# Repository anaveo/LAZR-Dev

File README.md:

# LAZR-Dev
LAZR is a remote which uses hand gestures to control functions of a TV. I undertook this project to understand IR signals and learn Autodesk Eagle, a PCB design software.

For more information click [here](https://omanavekar.wixsite.com/ommakes/lazr) to access LAZR's page on [omlabs.me](https://omanavekar.wixsite.com/ommakes)

## Components
| Plugin | Quantity | Description |
| ------ | ------ | ------ |
| Node MCU | 1 | Microcontroller Unit |
| Flex Sensor | 5 | Sense finger movement |
| 1k Resistor | 5 | Voltage dividing resistor for flex sensor |
| 74HX4051N | 1 | Multiplexer IC for sensors |
| DIP-8 IC Socket | 1 | Multiplexer IC mount |
| Pin Header | 40 | - |
| Jumper Cable | 10 | - |
| Glove | 1 | - |
| PCB | 1 | - |

## Software
* [Arduino IDE](https://www.arduino.cc/en/main/software) - Programming environment
* [Autodesk EAGLE](https://www.autodesk.com/products/eagle/overview?plc=F360&term=1-YEAR&support=ADVANCED&quantity=1) - Schematic and PCB design software

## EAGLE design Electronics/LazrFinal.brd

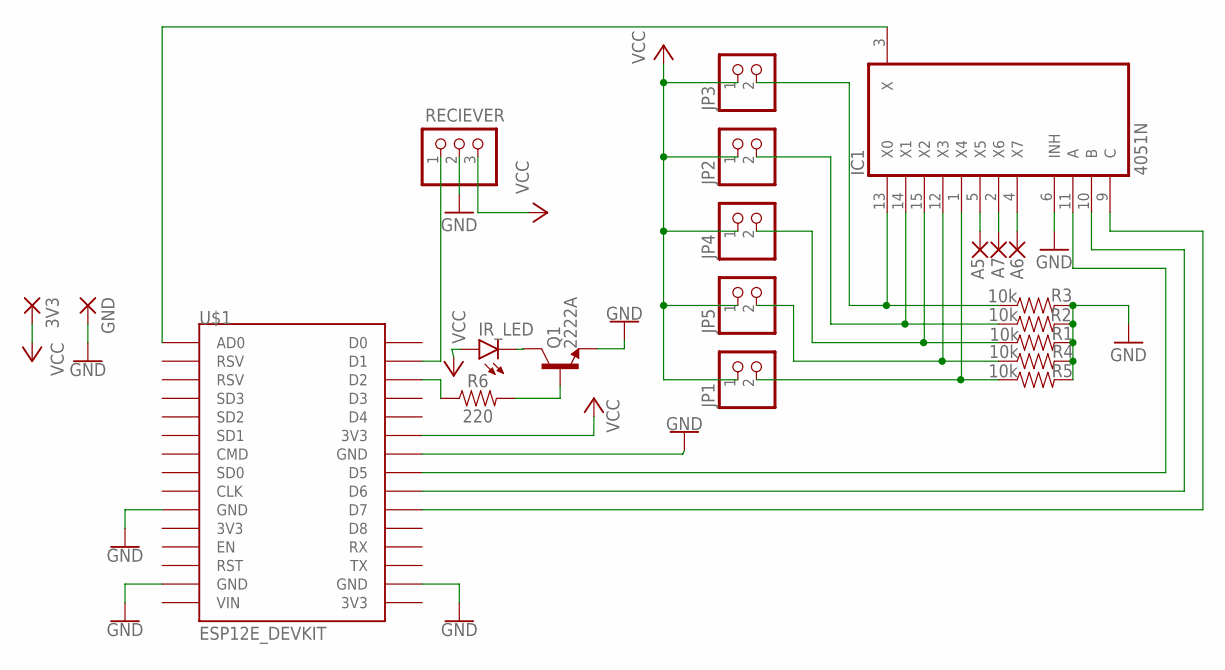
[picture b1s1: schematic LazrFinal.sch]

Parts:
3V3: SMD5; SMD2,54-5,08
A5, A6, A7: SMD2; SMD1,27-2,54
GND: SMD5; SMD2,54-5,08
IC1: 4051N; DIL16
IR_LED: LED-IRTSAL6100; LED_5MM
JP1, JP2, JP3, JP4, JP5: PINHD-1X2; 1X02
Q1: 2222A; TO-92
R1, R2, R3, R4, R5: 10k; AXIAL-0.3
R6: 220; AXIAL-0.3
RECIEVER: PINHD-1X3; 1X03
U$1: ESP12E_DEVKIT

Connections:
GND: GND.1, IC1.6 (INH), IC1.8 (GND), Q1.1 (E), R1.P$2 (2), R2.P$2 (2), R3.P$2 (2), R4.P$2 (2), R5.P$2 (2), RECIEVER.2, U$1.GND@0 (GND), U$1.GND@1 (GND), U$1.GND@2 (GND), U$1.GND@3 (GND)
unnamed: IC1.3 (X), U$1.AD0
unnamed: IC1.11 (A), U$1.D5
unnamed: IC1.10 (B), U$1.D6
unnamed: IC1.9 (C), U$1.D7
unnamed: IC1.13 (X0), JP3.2, R3.P$1 (1)
unnamed: IC1.14 (X1), JP2.2, R2.P$1 (1)
unnamed: IC1.15 (X2), JP4.2, R1.P$1 (1)
unnamed: IC1.12 (X3), JP5.2, R4.P$1 (1)
unnamed: IC1.1 (X4), JP1.2, R5.P$1 (1)
unnamed: R6.P$1 (1), U$1.D2
unnamed: RECIEVER.1, U$1.D1
unnamed: IR_LED.K (C), Q1.3 (C)
unnamed: Q1.2 (B), R6.P$2 (2)
unnamed: A5.1, IC1.5 (X5)
unnamed: A7.1, IC1.2 (X6)
unnamed: A6.1, IC1.4 (X7)
VCC: 3V3.1, IC1.16 (VCC), IR_LED.A, JP1.1, JP2.1, JP3.1, JP4.1, JP5.1, RECIEVER.3, U$1.3V3@1 (3V3)
VEE: IC1.7 (VEE)

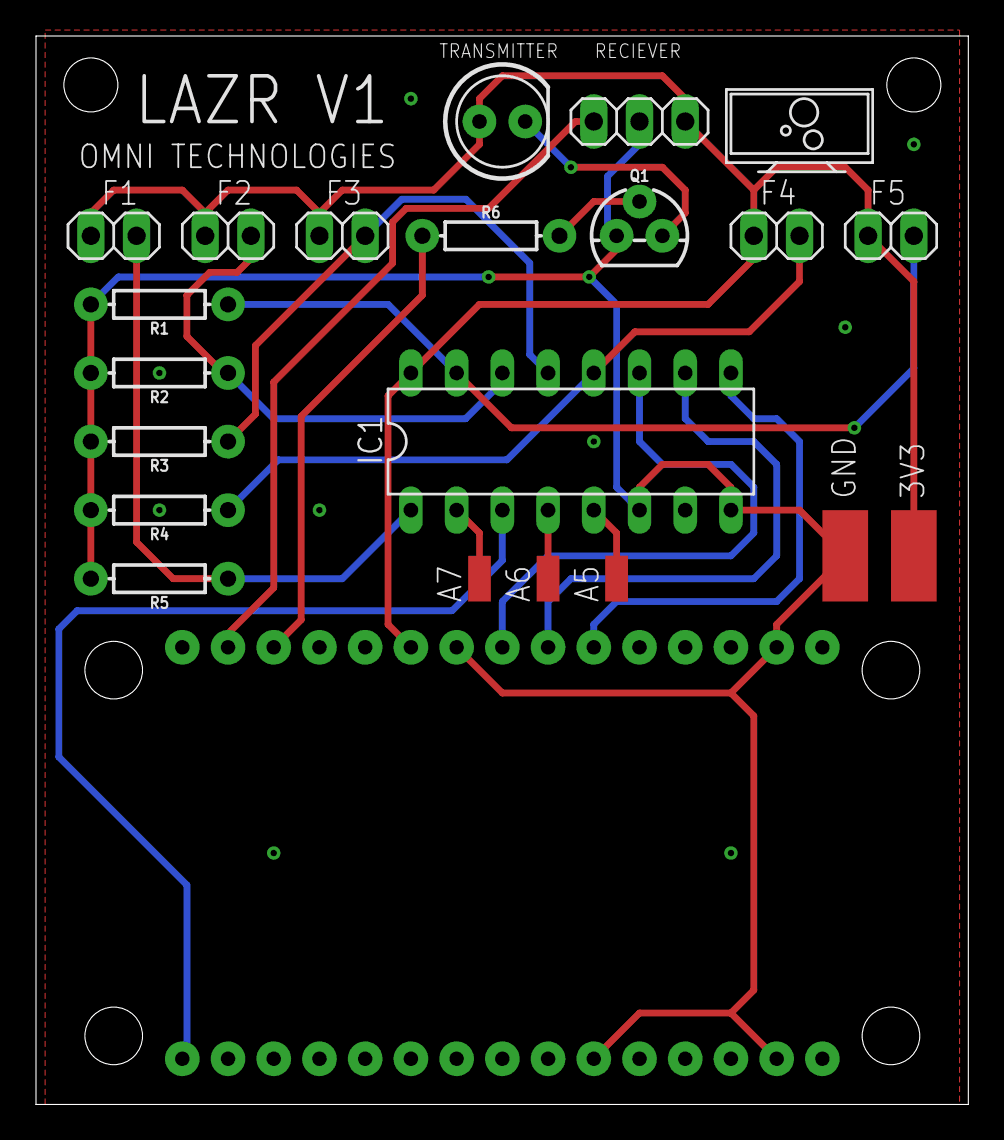
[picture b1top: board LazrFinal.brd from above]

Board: 2 copper layers, 51.8 x 59.4 mm, 21 parts (0 on the bottom side), 18 nets.

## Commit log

2020-06-08 Add LAZR software
2020-06-08 PCB file
2020-06-08 Schematic File
2020-06-08 Create gitkeep
2020-06-08 Rename LazrFinal.brd to Electronics/LazrFinal.brd
2020-06-08 Rename LazrFinal.sch to Electronics/LazrFinal.sch
2020-06-08 Rename Lazr_Software_Rev2.ino to Software/Lazr_Software_Rev2.ino

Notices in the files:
parts and their libraries:
SparkFun-LED: Licensing: Creative Commons ShareAlike 4.0 International - https://creativecommons.org/licenses/by-sa/4.0
